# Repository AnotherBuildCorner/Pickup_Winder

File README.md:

# Pickup Coil Winder. V2
Tried looking for pickup winders on the internet, only to be blown away by the crazy price tags?

I bet you've tried the old school method of a Drill and your fingers, and I can also guess it didn't go well either.

Want the ability to wind a picckup bobbin, without breaking the bank, and without having to sit there with laser focus trying to keep that 42 gauge wire from breaking while the cat is in the way?

Then this design might just be what you need!

Based off of commonly available Hobby RC components, and an ESP32 microcontroller. With a small handful of 3D printed components added, this device can wind all your common guitar pickup bobbins with minimal user input.

### Overview:
At the heart of this design is a simple IO PCB with a 5V linear regulator, ESP32, and pin headers to connect other components

And a 3D printed mechanics housing, integrating a 550 sized RC motor, 4:1 Pulley drive, 5mm bearing rod and bearings, encoder wheel, optical sensor, and optional Hall effect sensor
### (Full Drive Assembly model)

Assembly Video

https://github.com/AnotherBuildCorner/Pickup_Winder/assets/112969078/35dab373-d6de-44d6-9a98-b22964a5057d

### Motor and Esc

### Housing

### Optical Encoder Wheel

### Large Pulley

### Small Pulley

### Optical Encoder location

### Hosuing with Hall Effect Sensor

### Annotated image:

On top Panel are three things: The OLED readout, the traverse servo and cradle, and the Wire tensioner/guide assembly.
The oled is a simple Adafruit 1306 OLED  128X64. in a custom holder
### OLED Holder

The Traverse servo is a commonly available SG90 micro servo located in a 3d printed dovetail cradle with spring tension
### Traverse Servo Assembly

and the wire tensioner is a simple piece of plexiglass with a smooth hole in one end, with a pair of Cymbal felts tensioned by a bolt. The wire passes between the felts, and through a hole in the arm of the servo before being wound to the bobbin.

## Schematic

## Design Choices
### Why the RC components
Initially, back in V 0.5, a stepper motor driver was used instead of RC motors, which eliminates the need for other encoders.

However this proved unreliable in testing, as the motor torque was terrible, the drive would sometimes get confused and reverse, ruining the bobbin, and the stepper libraries caused the motor to ramp up and down in speed for the auto traverse.

At the time I also had some RC components laying about, and decided to try them as they were "free to me". And for a system to control the auto traverse, a micro servo was the simplest method available since all that's needed is a servo library and micro controller. 

### Belt Drive?
So i've tried direct drive, Gear drive, and belt drive.  They all have pros and cons.

For the direct drive. Motor selection becomes a primary concern. as 550 size RC motors are available in a multitude of torque and speed configurations defined by their turn count.

Problem is these motors are meant to run several thousand RPM. So the 1000 RPM needed is hard to control, and the speed jumps from too slow, to too fast easily. Plus the most commonly available motors don't have enough torque.

Also, if a hall effect sensor is added. the magnet is mounted to the drive flange, which causes instability at high speeds.

So, gear drive?
Two problems here. One is the geartrain to get a 4:1 reduction, as well as enough distance between motor and drive flange. is HUGE. 

Also, the noise was unbearable.

Belt drive on the other hand, has but one major downside over direct drive.  The additional bearings and shafts needed to support the drive flange add cost. 

5mm bore pulleys are easily obtainable and inexpensive. In fact, future versions may receive a CNC style timing belt drive.

### Why not an Arduino?
For a few reasons
One, Arduinos lack the general IO I wanted/needed to upgrade this system.  Version 1 was driven off of a Nano, and couldn't handle the inclusion of a rotary encoder

Two, I have a few ESP32's laying around from other projects, as well as experience using them

Three, ESP32's are Arduino code enabled. So no need to change code base

Four, ESP32's have integrated WiFi, Bluetooth, and Serial Coms. So if the desire should ever strike to create a webpage to control the winder, or maybe an app. The device is already ready to do so.

Five, ESP32's are pretty inexpensive. For the one I used, $10 for a 5MHz clock, around 20 available GPIO, and the communications above? No Brainer in my book.

## Features:

At present the enabled features are:
- Serial communication readout
- Multi screen OLED readout, including estimted DC resistance, wire length usage, and RPM
- Auto Traverse with multiple winding patterns available
- Variable speed and direction control with Auto Stop
- Multiple parameter adjustment, including:
  + Bobbin Size
  + Wire Gauge
  + Insulation Thickness
  + Winding Pattern
  + Faceplate Offset
  + Wind Count
  + Under/Overwind
  + Error margin
- Presets enabled via code edit
- Manual adjustment of winding via joystick control
- 
In the future a set of coded presets will be included and enabled via the Encoder knob and OLED. With the ability to adjust parameters after a preset is selected. This will completely untether the unit from a computer for general usage.

## Parts list
Note, some of these parts come in multiple quantites, prices reflect a Price Per in most cases
- 550 Motor and ESC, $30
- ESP32 Devkit-C V4, $10
- SG90 Micro Servo, $2.50
- Support Bearings, $2
- Drive Shaft, $2
- PCB, $8 for 5, with S&H included (minimum order)
- Cymbal Felts, $4
- Optical Sensor, $1
- Potentiometer, $1
- OLED, $5
- Rotary Encoder, $2
- Switch, $1
- Drive Belt material, $5
- Main Drive flange, $4

Links Will be added at a later date.  

## But what about those 3D parts
Critically, none of the 3D printed parts are a deal breaker for the design. The original V1 design (located below) used a plexiglass mount plate and no 3D printed parts.

The belt drive tower can easily be fashioned from a pair of plates, perhaps even wood. So long as the motor can be mounted to it via the faceplate screws, and the bearings fit with enough space for the encoder wheel, the rest is optional. 

The encoder wheel could be simply made with a block of material with a hole through the center, colored white on one side, and black on the other.

the servo cradle is a nice but not required extra. The original was held down by a plate secured with two screws (see V1 below)

The control box isn't required, just makes things a little nicer to look at. A simple piece of thin stock with holes cut in for the power jack, knobs, and switch is all that's needed.

## Some parts iterations.

### Previous version, and Gear drive towers

### Changes to pulleys 

### Servo cradle designs

## Original V1 design

The original design utilized an Arduino Nano microcontroller, with a direct drive motor, and custom infared light gate. With a circuit board built on a solderable breadboard. This functioned as an excelent prototype but had a few key problems I wanted to update.

First and foremost, direct drive has it's downsides. While being the quietest operation, it requires specific motor selection to achieve, as 550 size RC motors are classed by turn count, with 12T being a low torque high speed, and up to 80T being high torque Low speed.  Problem is 12T models are the most commonly available, and the speed controller can't control them effectively at the 1000 RPM range, and the available torque is borderline too low to overcome the wire tension.

Additionally, the direct drive requires adding the magnet to the flywheel for the hall sensor. This causes vibrations near the top speed.
Lastly, the Nano lacked the complete GPIO desired to run an OLED, encoder, servo, potentiometer, switch, and extras.
With the lack of an OLED and encoder, the system was permanently tethered to a computer for serial programming and monitoring.

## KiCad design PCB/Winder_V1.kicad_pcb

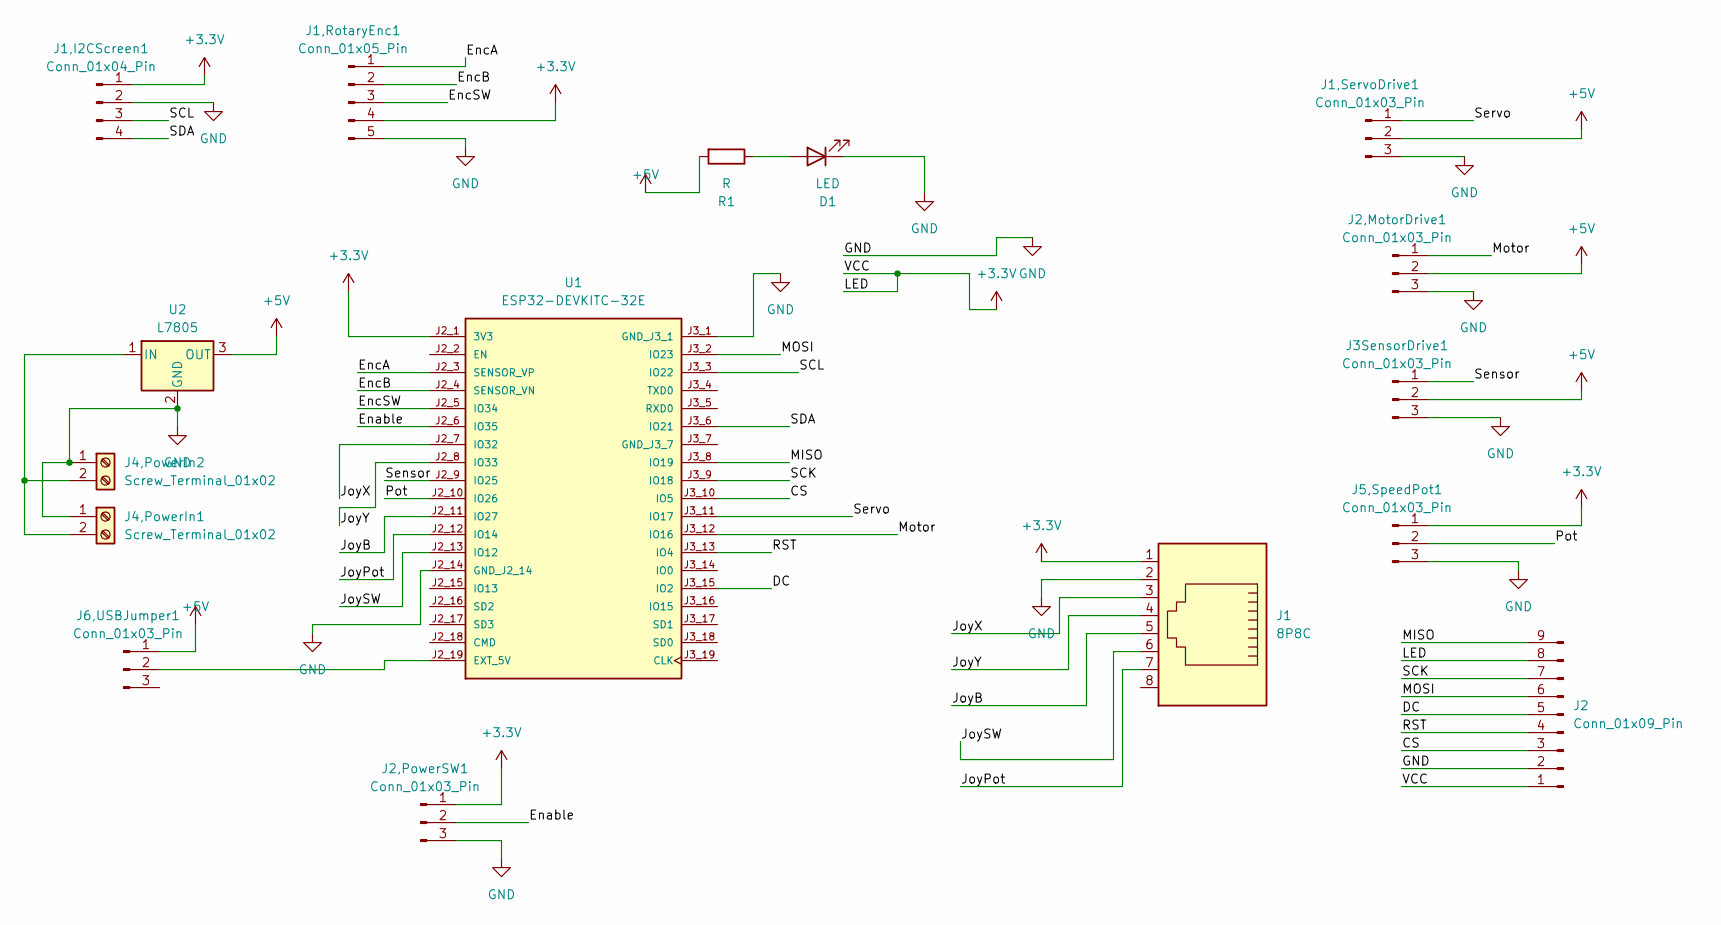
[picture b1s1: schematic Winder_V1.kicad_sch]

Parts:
D1: LED; LED_D5.0mm
J1: 8P8C; RJ45_Amphenol_54602-x08_Horizontal
J1,I2CScreen1: Conn_01x04_Pin; PinHeader_1x04_P2.54mm_Vertical
J1,RotaryEnc1: Conn_01x05_Pin; PinHeader_1x05_P2.54mm_Vertical
J1,ServoDrive1, J2,MotorDrive1, J2,PowerSW1, J3SensorDrive1, J5,SpeedPot1, J6,USBJumper1: Conn_01x03_Pin; PinHeader_1x03_P2.54mm_Vertical
J2: Conn_01x09_Pin; PinHeader_1x09_P2.54mm_Vertical
J4,PowerIn1, J4,PowerIn2: Screw_Terminal_01x02; TerminalBlock_4Ucon_1x02_P3.50mm_Horizontal
R1: R; R_Axial_DIN0207_L6.3mm_D2.5mm_P10.16mm_Horizontal
U1: ESP32-DEVKITC-32E; MODULE_ESP32-DEVKITC-32E; PARTREV 1.4
U2: L7805; TO-220-3_Vertical

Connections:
+3.3V: J1.1, J1,I2CScreen1.1, J1,RotaryEnc1.4, J2.1, J2.8, J2,PowerSW1.1, J5,SpeedPot1.1, U1.J2_1 (3V3)
+5V: J1,ServoDrive1.2, J2,MotorDrive1.2, J3SensorDrive1.2, J6,USBJumper1.1, R1.2, U2.3 (OUT)
/CS: J2.3, U1.J3_10 (IO5)
/DC: J2.5, U1.J3_15 (IO2)
/Enable: J2,PowerSW1.2, U1.J2_6 (IO35)
/EncA: J1,RotaryEnc1.1, U1.J2_3 (SENSOR_VP)
/EncB: J1,RotaryEnc1.2, U1.J2_4 (SENSOR_VN)
/EncSW: J1,RotaryEnc1.3, U1.J2_5 (IO34)
/JoyB: J1.5, U1.J2_11 (IO27)
/JoyPot: J1.7, U1.J2_12 (IO14)
/JoySW: J1.6, U1.J2_13 (IO12)
/JoyX: J1.3, U1.J2_7 (IO32)
/JoyY: J1.4, U1.J2_8 (IO33)
/MISO: J2.9, U1.J3_8 (IO19)
/MOSI: J2.6, U1.J3_2 (IO23)
/Motor: J2,MotorDrive1.1, U1.J3_12 (IO16)
/Pot: J5,SpeedPot1.2, U1.J2_10 (IO26)
/RST: J2.4, U1.J3_13 (IO4)
/SCK: J2.7, U1.J3_9 (IO18)
/SCL: J1,I2CScreen1.3, U1.J3_3 (IO22)
/SDA: J1,I2CScreen1.4, U1.J3_6 (IO21)
/Sensor: J3SensorDrive1.1, U1.J2_9 (IO25)
/Servo: J1,ServoDrive1.1, U1.J3_11 (IO17)
GND: D1.1 (K), J1.2, J1,I2CScreen1.2, J1,RotaryEnc1.5, J1,ServoDrive1.3, J2.2, J2,MotorDrive1.3, J2,PowerSW1.3, J3SensorDrive1.3, J4,PowerIn1.1, J4,PowerIn2.1, J5,SpeedPot1.3, U1.J2_14 (GND_J2_14), U1.J3_1 (GND_J3_1), U2.2 (GND)
unnamed: D1.2 (A), R1.1
unnamed: J4,PowerIn1.2, J4,PowerIn2.2, U2.1 (IN)
unnamed: J6,USBJumper1.2, U1.J2_19 (EXT_5V)

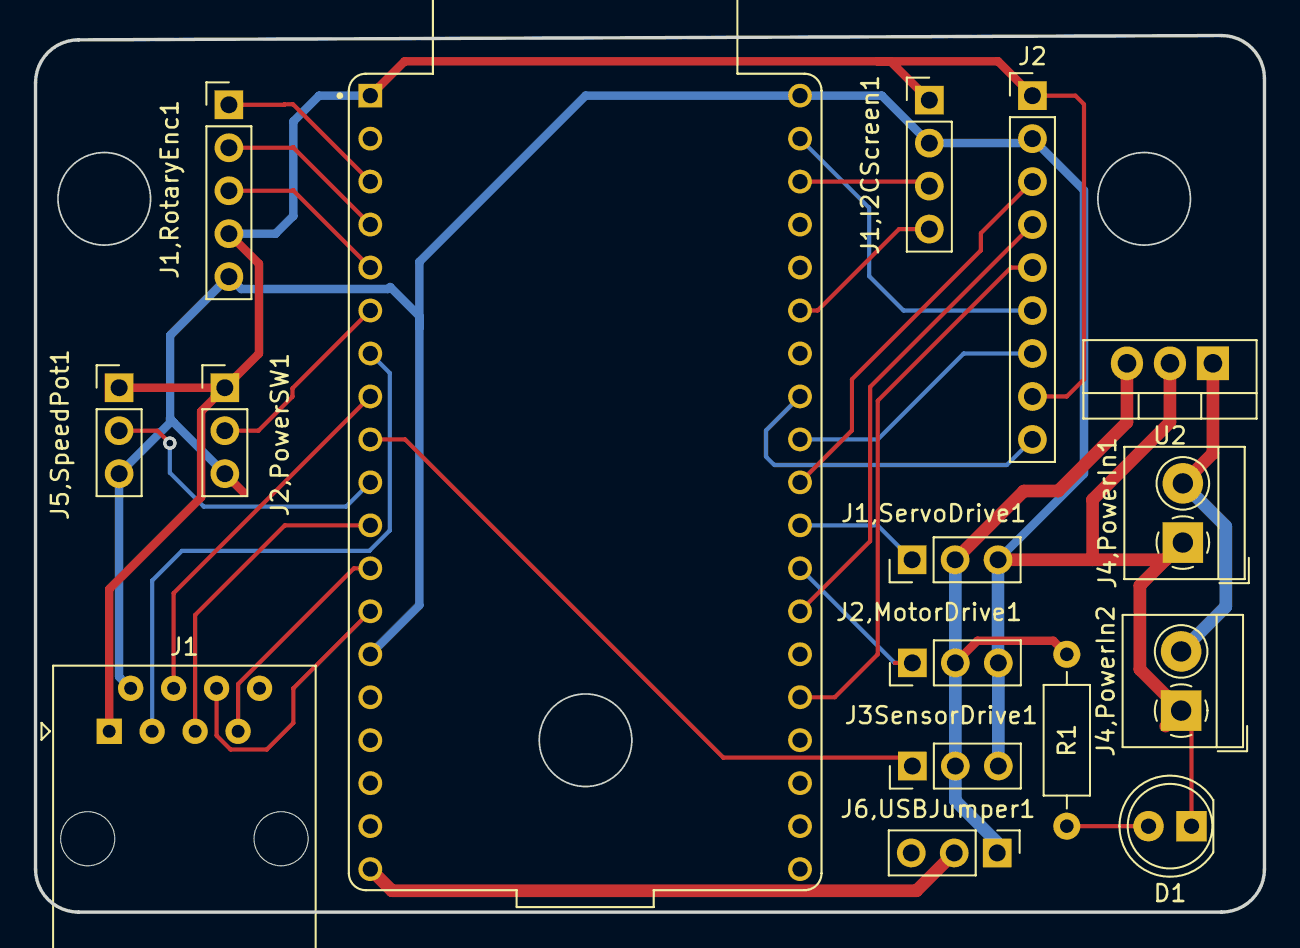
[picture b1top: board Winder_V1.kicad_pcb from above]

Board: 2 copper layers, 72.6 x 51.8 mm, 16 parts (0 on the bottom side), 27 nets.

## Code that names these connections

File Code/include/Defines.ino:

#include <Arduino.h>
#include <ESP32Servo.h>

#include <Adafruit_SSD1306.h>
#include <Adafruit_I2CDevice.h>
#include <Wire.h>
#include <SPI.h>
// Need to update for the ESP32 pinouts
#define GatePin 25

#define GateLED 9
#define GateLEDPwr 255
#define GateMin 0
#define GateMax 100

#define PotPin 26
#define Potmin 4095
#define Potmax 0

#define SwitchPin 35
#define ESCPin 16
#define ServoPin 17
#define CWMaxSpeed_Def 55 
#define CCWMaxSpeed_def 135
#define Stop 95
#define Spool  2
#define SpoolRPM 200

#define EncoderA 36 // Sensor VP  
#define EncoderB 39 // Sensor VN
#define EncoderSW 34

#define JoyX 32
#define JoyY 33
#define JoyB 27
#define JoyPot 14
#define JoySW 12

#define MOSI 23
#define MISO 

#define refresh 500
Servo ESC;
Servo servo;


void PinDeclare(){
pinMode(SwitchPin,INPUT_PULLUP);
pinMode(EncoderSW,INPUT_PULLUP);
pinMode(PotPin,INPUT);
pinMode(JoyX,INPUT);
pinMode(JoyY,INPUT);

  
}
//ccw vs cw.  6000 = 7.7k DCR, CW. 4.6 CCW 6000 vs 8000 makes same coil size

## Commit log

2024-05-28 Base Commit
2024-05-28 photos
2024-06-06 new photos
2024-09-05 minor updates
